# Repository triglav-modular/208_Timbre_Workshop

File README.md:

# 208 Timbre Workshop

Eurorack adaptation of the late 208 wavefolder section.

8 HP, adjustable input and output range.

BOM / Mouser cart: 
https://www.mouser.com/ProjectManager/ProjectDetail.aspx?AccessID=5e38aa6b9c

Sliders: https://hu.farnell.com/en-HU/alps/rs4511150k/potentiometer-slide-50k/dp/1191730

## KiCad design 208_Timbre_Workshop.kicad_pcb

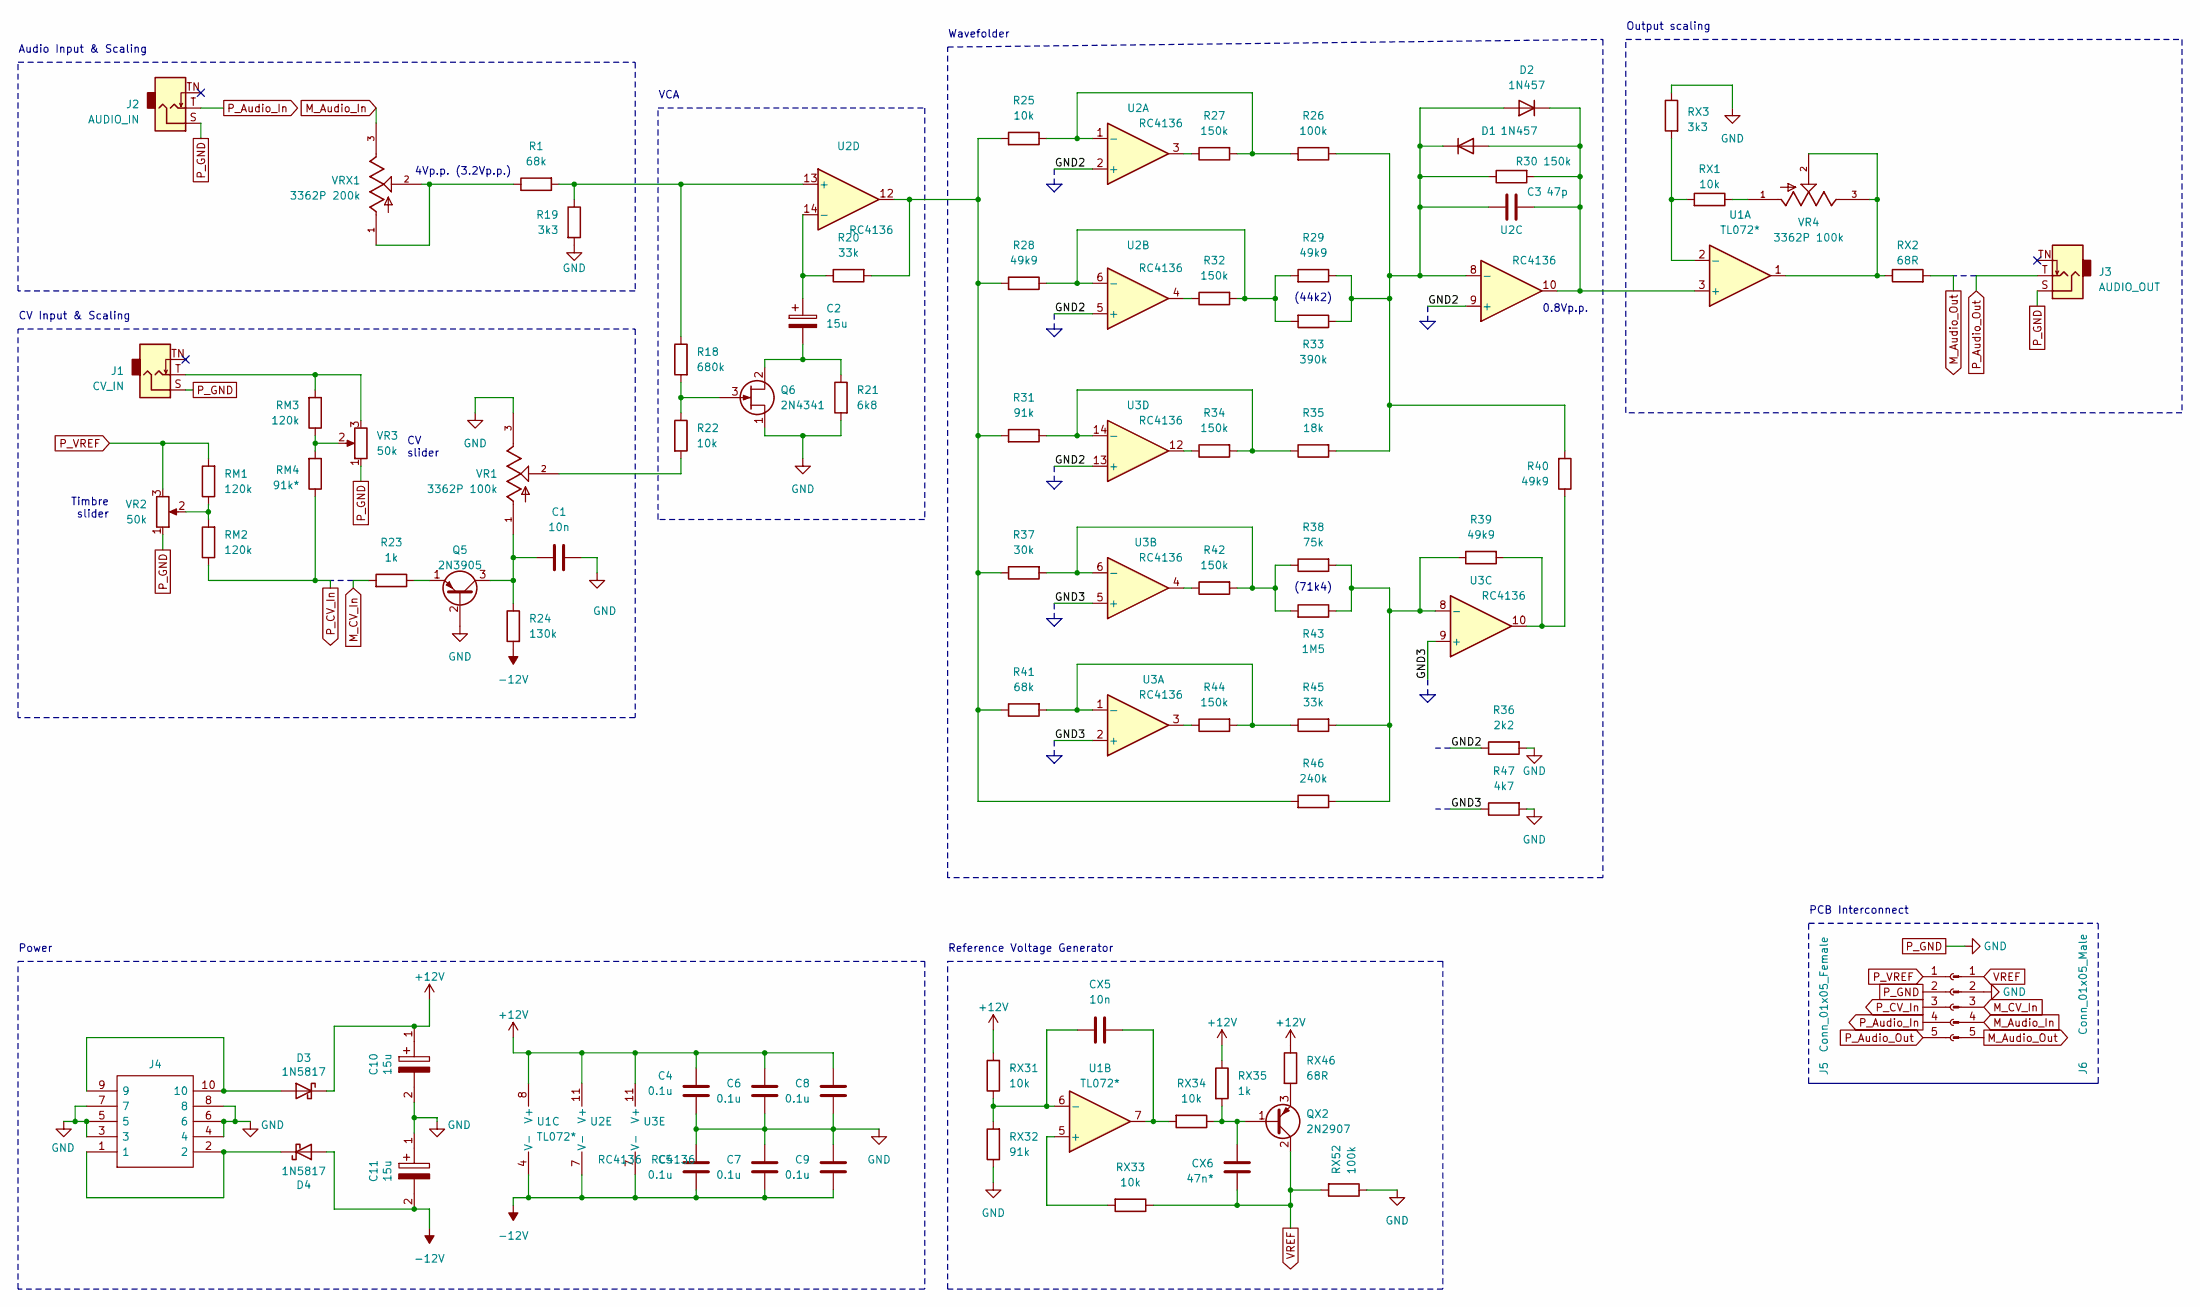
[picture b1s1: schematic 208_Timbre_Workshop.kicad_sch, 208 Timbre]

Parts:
C1: 10n; C_Disc_D7.0mm_W2.5mm_P5.00mm
C2: 15u; CP_Radial_D5.0mm_P2.00mm
C3: 47p; C_Disc_D7.0mm_W2.5mm_P5.00mm
C4, C5, C6, C7, C8, C9: 0.1u; C_Disc_D7.0mm_W2.5mm_P5.00mm
C10, C11: 15u; CP_Radial_D5.0mm_P2.00mm; Manufacturer_Part_Number EEE-FN1A470UR; Mouser Part Number 667-EEE-FN1A470UR
CX5: 10n; C_Disc_D7.0mm_W2.5mm_P5.00mm
CX6: 47n*; C_Disc_D7.0mm_W2.5mm_P5.00mm
D1, D2: 1N457; D_DO-35_SOD27_P7.62mm_Horizontal
D3, D4: 1N5817; D_DO-35_SOD27_P7.62mm_Horizontal
J1: CV_IN; THONKICONN
J2: AUDIO_IN; THONKICONN
J3: AUDIO_OUT; THONKICONN
J4: 30310-6002HB; Eurorack_Power; Manufacturer_Part_Number 30310-6002HB; Mouser Part Number 517-30310-6002
J5: Conn_01x05_Female; PinSocket_1x05_P2.54mm_Vertical
J6: Conn_01x05_Male; PinSocket_1x05_P2.54mm_Vertical
Q5: 2N3905; TO-92
Q6: 2N4341; TO-18-3
QX2: 2N2907; TO-92
R1, R41: 68k; R_Axial_DIN0207_L6.3mm_D2.5mm_P7.62mm_Horizontal
R18: 680k; R_Axial_DIN0207_L6.3mm_D2.5mm_P7.62mm_Horizontal
R19: 3k3; R_Axial_DIN0207_L6.3mm_D2.5mm_P7.62mm_Horizontal
R20, R45: 33k; R_Axial_DIN0207_L6.3mm_D2.5mm_P7.62mm_Horizontal
R21: 6k8; R_Axial_DIN0207_L6.3mm_D2.5mm_P7.62mm_Horizontal
R22, R25: 10k; R_Axial_DIN0207_L6.3mm_D2.5mm_P7.62mm_Horizontal
R23: 1k; R_Axial_DIN0207_L6.3mm_D2.5mm_P7.62mm_Horizontal
R24: 130k; R_Axial_DIN0207_L6.3mm_D2.5mm_P7.62mm_Horizontal
R26: 100k; R_Axial_DIN0207_L6.3mm_D2.5mm_P7.62mm_Horizontal
R27, R30, R32, R34, R42, R44: 150k; R_Axial_DIN0207_L6.3mm_D2.5mm_P7.62mm_Horizontal
R28, R29, R39, R40: 49k9; R_Axial_DIN0207_L6.3mm_D2.5mm_P7.62mm_Horizontal
R31: 91k; R_Axial_DIN0207_L6.3mm_D2.5mm_P7.62mm_Horizontal
R33: 390k; R_Axial_DIN0207_L6.3mm_D2.5mm_P7.62mm_Horizontal
R35: 18k; R_Axial_DIN0207_L6.3mm_D2.5mm_P7.62mm_Horizontal
R36: 2k2; R_Axial_DIN0207_L6.3mm_D2.5mm_P7.62mm_Horizontal
R37: 30k; R_Axial_DIN0207_L6.3mm_D2.5mm_P7.62mm_Horizontal
R38: 75k; R_Axial_DIN0207_L6.3mm_D2.5mm_P7.62mm_Horizontal
R43: 1M5; R_Axial_DIN0207_L6.3mm_D2.5mm_P7.62mm_Horizontal
R46: 240k; R_Axial_DIN0207_L6.3mm_D2.5mm_P7.62mm_Horizontal
R47: 4k7; R_Axial_DIN0207_L6.3mm_D2.5mm_P7.62mm_Horizontal
RM1, RM2, RM3: 120k; R_Axial_DIN0207_L6.3mm_D2.5mm_P7.62mm_Horizontal
RM4: 91k*; R_Axial_DIN0207_L6.3mm_D2.5mm_P7.62mm_Horizontal
RX1, RX31, RX33, RX34: 10k; R_Axial_DIN0207_L6.3mm_D2.5mm_P7.62mm_Horizontal
RX2, RX46: 68R; R_Axial_DIN0207_L6.3mm_D2.5mm_P7.62mm_Horizontal
RX3: 3k3; R_Axial_DIN0207_L6.3mm_D2.5mm_P7.62mm_Horizontal
RX32: 91k; R_Axial_DIN0207_L6.3mm_D2.5mm_P7.62mm_Horizontal
RX35: 1k; R_Axial_DIN0207_L6.3mm_D2.5mm_P7.62mm_Horizontal
RX52: 100k; R_Axial_DIN0207_L6.3mm_D2.5mm_P7.62mm_Horizontal
U1: TL072*; DIP-8_W7.62mm_Socket
U2, U3: RC4136; DIP-14_W7.62mm_Socket
VR1, VR4: 3362P 100k; BOURNS_3362P_TRIMMER; PARTREV 08/26/10
VR2, VR3: 50k; RS45111
VRX1: 3362P 200k; BOURNS_3362P_TRIMMER; PARTREV 08/26/10

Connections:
+12V: C4.2, C6.2, C8.2, C10.1, D3.1 (K), RX31.2, RX35.1, RX46.1, U1.8 (V+), U2.11 (V+), U3.11 (V+)
-12V: C5.1, C7.1, C9.1, C11.2, D4.2 (A), R24.2, U1.4 (V-), U2.7 (V-), U3.7 (V-)
/GND2: R36.1, U2.2 (+), U2.5 (+), U2.9 (+), U3.13 (+)
/GND3: R47.1, U3.2 (+), U3.5 (+), U3.9 (+)
M_Audio_In: J6.4, VRX1.3
M_Audio_Out: J6.5, RX2.2
M_CV_In: J6.3, R23.2
unnamed: CX5.2, RX34.2, U1.7
unnamed: C3.2, D1.2 (A), D2.1 (K), R30.2, U1.3 (+), U2.10
unnamed: C3.1, D1.1 (K), D2.2 (A), R26.1, R29.1, R30.1, R33.1, R35.2, R40.2, U2.8 (-)
unnamed: D3.2 (A), J4.9, J4.10
unnamed: D4.1 (K), J4.1, J4.2
unnamed: J1.T, RM3.2, VR3.3
unnamed: C1.1, Q5.3 (C), R24.1, VR1.1
unnamed: Q5.1 (E), R23.1
unnamed: C2.2, Q6.2 (D), R21.1
unnamed: Q6.3 (G), R18.2, R22.1
unnamed: CX6.2, QX2.1 (B), RX34.1, RX35.2
unnamed: QX2.3 (E), RX46.2
unnamed: R1.1, VRX1.1, VRX1.2
unnamed: R20.2, R25.2, R28.2, R31.2, R37.1, R41.1, R46.2, U2.12
unnamed: R22.2, VR1.2
unnamed: R27.1, U2.3
unnamed: R32.1, U2.4
unnamed: R34.1, U3.12
unnamed: R39.2, R40.1, U3.10
unnamed: R42.1, U3.4
unnamed: R44.1, U3.3
unnamed: RM1.1, RM2.2, VR2.2
unnamed: RM3.1, RM4.2, VR3.2
unnamed: RX1.1, VR4.1
unnamed: RX2.1, U1.1, VR4.2, VR4.3
unnamed: RX1.2, RX3.2, U1.2 (-)
unnamed: RX33.2, U1.5 (+)
unnamed: CX5.1, RX31.1, RX32.2, U1.6 (-)
unnamed: R25.1, R26.2, R27.2, U2.1 (-)
unnamed: R28.1, R29.2, R32.2, R33.2, U2.6 (-)
unnamed: R1.2, R18.1, R19.1, U2.13 (+)
unnamed: C2.1, R20.1, U2.14 (-)
unnamed: R41.2, R44.2, R45.1, U3.1 (-)
unnamed: R37.2, R38.1, R42.2, R43.2, U3.6 (-)
unnamed: R38.2, R39.1, R43.1, R45.2, R46.1, U3.8 (-)
unnamed: R31.1, R34.2, R35.1, U3.14 (-)
P_Audio_In: J2.T, J5.4
P_Audio_Out: J3.T, J5.5
P_CV_In: J5.3, RM2.1, RM4.1
P_GND: C1.2, C4.1, C5.2, C6.1, C7.2, C8.1, C9.2, C10.2, C11.1, J1.S, J2.S, J3.S, J4.3, J4.4, J4.5, J4.6, J4.7, J4.8, J5.2, J6.2, Q5.2 (B), Q6.1 (S), R19.2, R21.2, R36.2, R47.2, RX3.1, RX32.1, RX52.1, VR1.3, VR2.1, VR3.1
P_VREF: J5.1, RM1.2, VR2.3
VREF: CX6.1, J6.1, QX2.2 (C), RX33.1, RX52.2

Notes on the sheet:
4Vp.p. (3.2Vp.p.)
Timbre slider
Wavefolder
PCB Interconnect
Power
CV slider
Reference Voltage Generator
VCA
(71k4)
Output scaling
CV Input & Scaling
0.8Vp.p.
Audio Input & Scaling
(44k2)

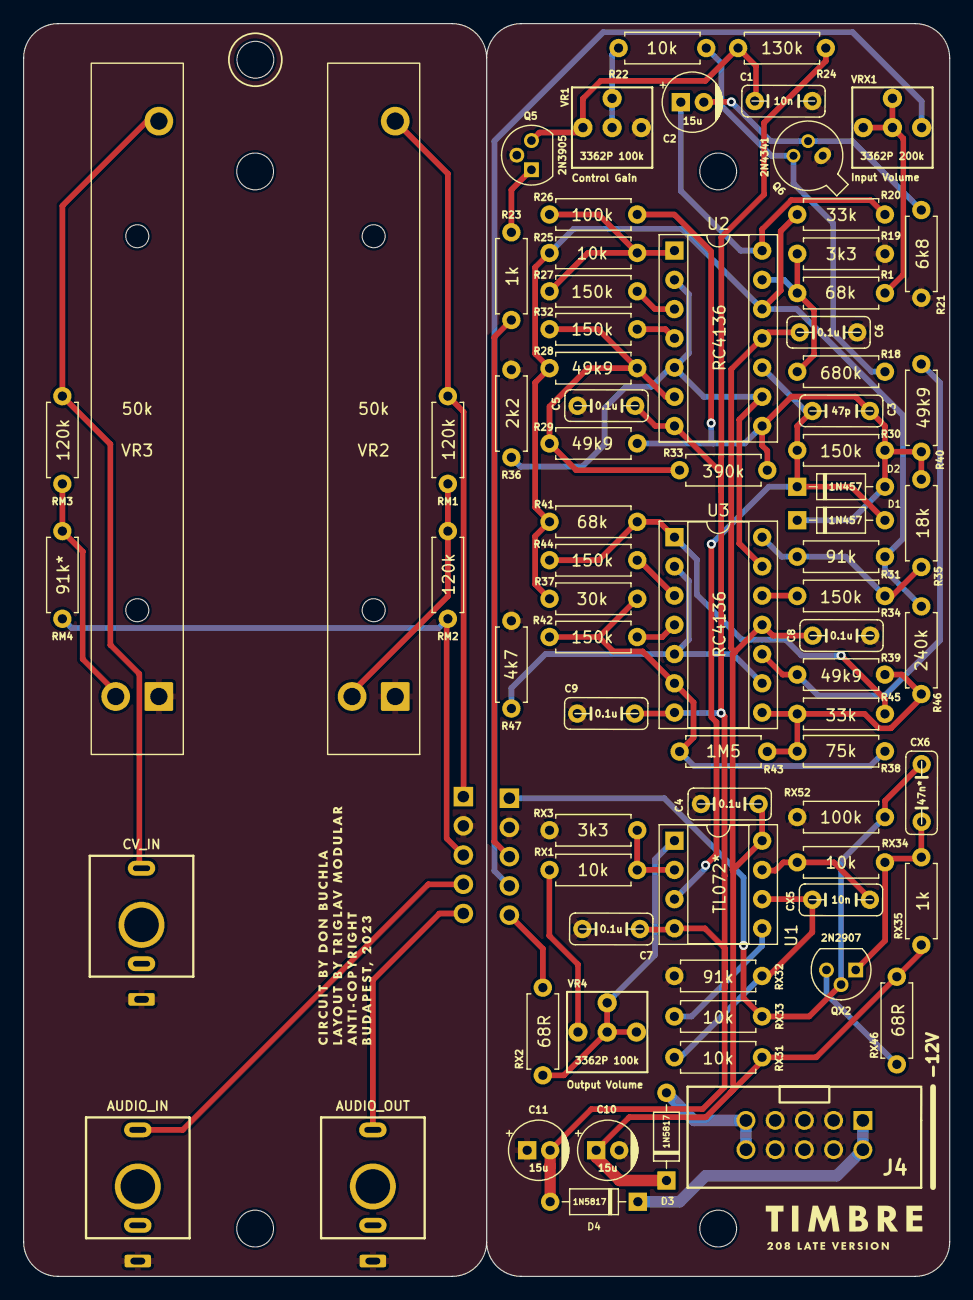
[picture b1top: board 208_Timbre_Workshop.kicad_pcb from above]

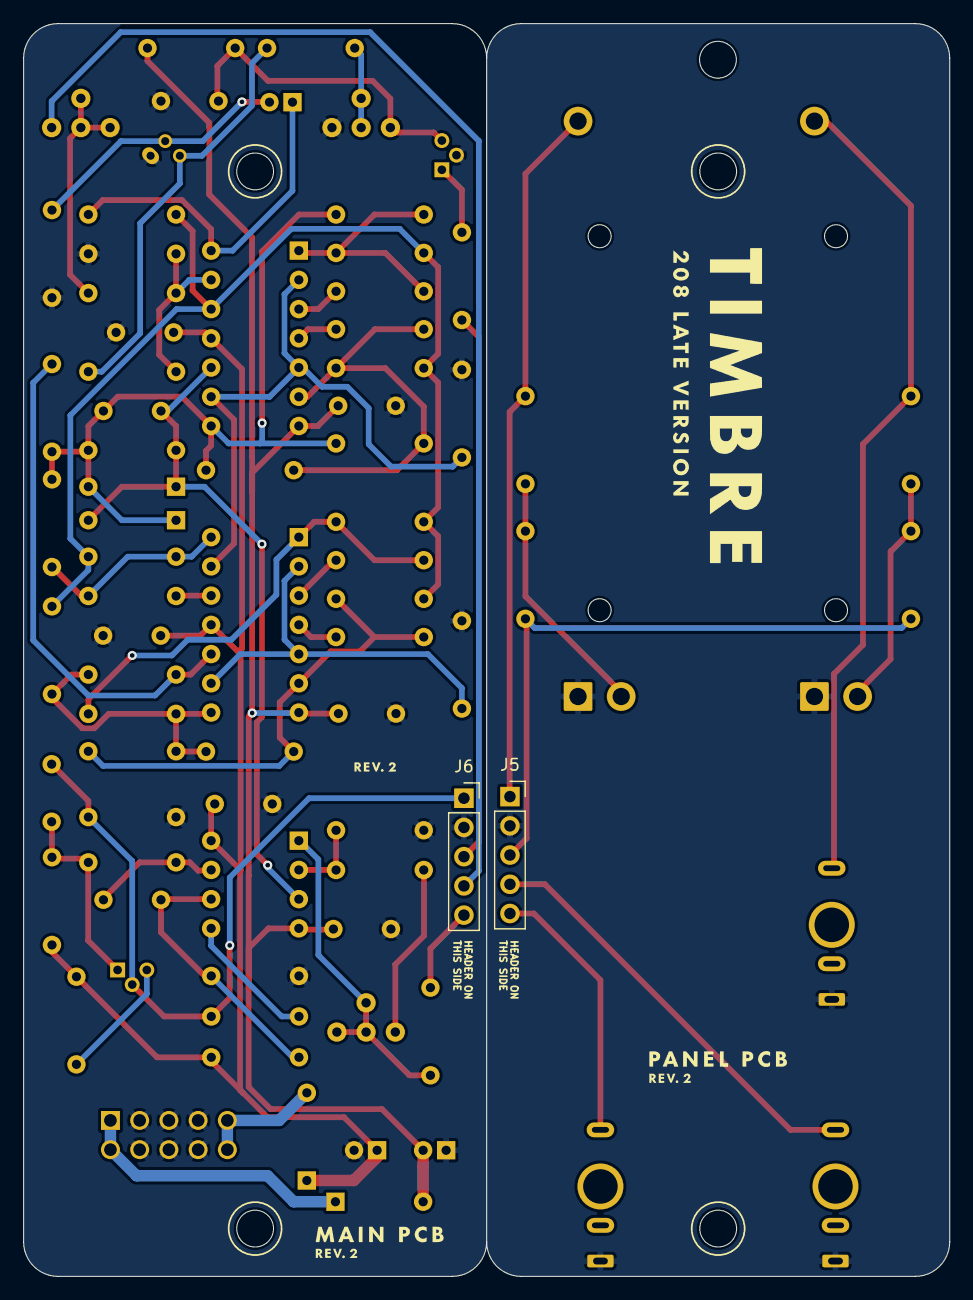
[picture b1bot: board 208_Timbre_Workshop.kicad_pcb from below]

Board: 2 copper layers, 80.5 x 108.9 mm, 79 parts (2 on the bottom side), 49 nets.

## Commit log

2023-03-18 alignment, transistor pins
2023-04-25 Cleanup
2023-04-26 Schematic update
2023-05-11 transistor update
2023-07-29 Rev. 2
2023-07-29 Rev.2
